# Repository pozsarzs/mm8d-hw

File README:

*** WARNING! It is not yet useable, because it is under development. WARNING ***

Short information
-----------------
MM8D/PC * Growing house controlling and remote monitoring device
Copyright (C) 2020 Pozsár Zsolt <pozsar.zsolt@szerafingomba.hu>
Homepage: <http://www.szerafingomba.hu/equipments/>

Documentation
 - version:             1.0
 - licence:             CC-BY-NC-4.0
 - language:            en

Hardware
 - version:             vyymmdd
 - architecture:        i386
 - operation system:    FreeDOS

Software
 - version:             v0.1
 - licence:             EUPL v1.1
 - language:            en

External libraries in package

*** WARNING! It is not yet useable, because it is under development. WARNING ***

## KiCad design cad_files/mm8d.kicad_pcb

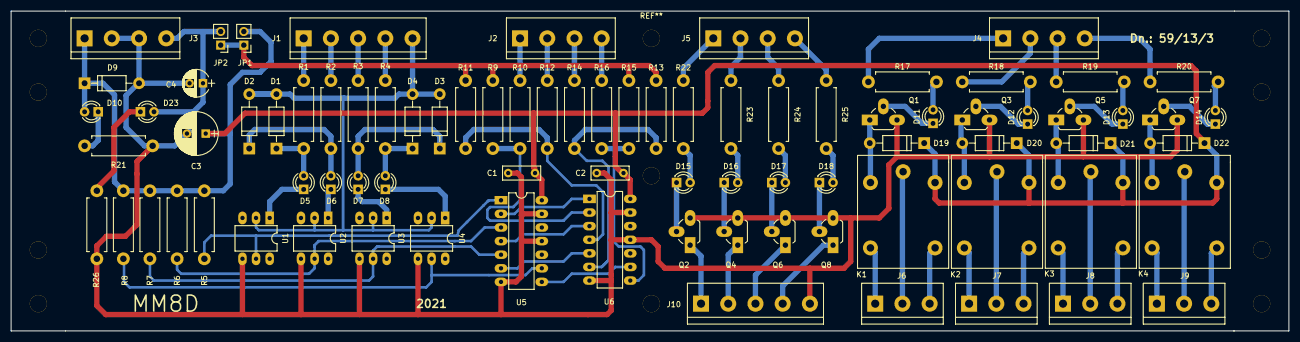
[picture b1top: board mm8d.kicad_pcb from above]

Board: 2 copper layers, 238.5 x 59.7 mm, 83 parts (0 on the bottom side), 79 nets.

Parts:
C1, C2: 100n; C_Rect_L7.0mm_W2.5mm_P5.00mm
C3: 470u; CP_Radial_D8.0mm_P3.50mm
C4: 4.7u; CP_Radial_D5.0mm_P2.50mm
D1, D2, D3, D4, D9, D19, D20, D21, D22: 1N4001; D_DO-41_SOD81_P10.16mm_Horizontal
D5, D6, D7, D8, D10, D11, D12, D13, D14, D15, D16, D17, D18, D23: LED; LED_D3.0mm
J1, J10: Screw_Terminal_1x05; bornier5
J2, J3, J4, J5: Screw_Terminal_1x04; bornier4
J6, J7, J8, J9: Screw_Terminal_1x03; bornier3
JP1: Jumper_NC_Small; Socket_Strip_Straight_1x02_Pitch2.54mm
JP2: Jumper_NO_Small; Socket_Strip_Straight_1x02_Pitch2.54mm
K1, K2, K3, K4: LEG-5; relay_leg
Q1, Q2, Q3, Q4, Q5, Q6, Q7, Q8: BC548C; TO-92_Rugged
R1, R2, R3, R4: 3.9k; R_Axial_DIN0411_L9.9mm_D3.6mm_P12.70mm_Horizontal
R5, R6, R7, R8, R9, R11, R13, R15: 4.7k; R_Axial_DIN0411_L9.9mm_D3.6mm_P12.70mm_Horizontal
R10, R12, R14, R16: 750; R_Axial_DIN0411_L9.9mm_D3.6mm_P12.70mm_Horizontal
R17, R18, R19, R20, R22, R23, R24, R25, R26: 620; R_Axial_DIN0411_L9.9mm_D3.6mm_P12.70mm_Horizontal
R21: 1k; R_Axial_DIN0411_L9.9mm_D3.6mm_P12.70mm_Horizontal
U1, U2, U3, U4: 4N25; DIP-6_W7.62mm_LongPads
U5: 74LS14; DIP-14_W7.62mm_LongPads
U6: 74LS05; DIP-14_W7.62mm_LongPads

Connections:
GND: C1.2, C2.2, C3.2, C4.2, D9.2, J3.2, J3.3, J10.5, Q1.3, Q2.3, Q3.3, Q4.3, Q5.3, Q6.3, Q7.3, Q8.3, R21.2, R26.2, U1.4, U2.4, U3.4, U4.4, U5.7, U5.11, U5.13, U6.7, U6.11, U6.13
unnamed: C4.1, D23.2, J3.4, JP2.2
unnamed: D1.1, D5.2, R1.1
unnamed: D1.2, D2.2, D3.2, D4.2, J1.5, U1.2, U2.2, U3.2, U4.2
unnamed: D2.1, D6.2, R2.1
unnamed: D3.1, D7.2, R3.1
unnamed: D4.1, D8.2, R4.1
unnamed: D5.1, U1.1
unnamed: D6.1, U2.1
unnamed: D7.1, U3.1
unnamed: D8.1, U4.1
unnamed: D10.1, R21.1
unnamed: D11.1, Q1.2
unnamed: D11.2, R17.2
unnamed: D12.1, Q3.2
unnamed: D12.2, R18.2
unnamed: D13.1, Q5.2
unnamed: D13.2, R19.2
unnamed: D14.1, Q7.2
unnamed: D14.2, R20.2
unnamed: D15.1, Q2.2
unnamed: D15.2, R22.2
unnamed: D16.1, Q4.2
unnamed: D16.2, R23.2
unnamed: D17.1, Q6.2
unnamed: D17.2, R24.2
unnamed: D18.1, Q8.2
unnamed: D18.2, R25.2
unnamed: D19.2, K1.2, Q1.1
unnamed: D20.2, K2.2, Q3.1
unnamed: D21.2, K3.2, Q5.1
unnamed: D22.2, K4.2, Q7.1
unnamed: D23.1, R26.1
unnamed: J1.1, R1.2
unnamed: J1.2, R2.2
unnamed: J1.3, R3.2
unnamed: J1.4, R4.2
unnamed: J2.1, R10.1
unnamed: J2.2, R12.1
unnamed: J2.3, R14.1
unnamed: J2.4, R16.1
unnamed: J4.1, R17.1
unnamed: J4.2, R18.1
unnamed: J4.3, R19.1
unnamed: J4.4, R20.1
unnamed: J5.1, R22.1
unnamed: J5.2, R23.1
unnamed: J5.3, R24.1
unnamed: J5.4, R25.1
unnamed: J6.1, K1.5
unnamed: J6.2, K1.3
unnamed: J6.3, K1.4
unnamed: J7.1, K2.5
unnamed: J7.2, K2.3
unnamed: J7.3, K2.4
unnamed: J8.1, K3.5
unnamed: J8.2, K3.3
unnamed: J8.3, K3.4
unnamed: J9.1, K4.5
unnamed: J9.2, K4.3
unnamed: J9.3, K4.4
unnamed: J10.1, Q2.1
unnamed: J10.2, Q4.1
unnamed: J10.3, Q6.1
unnamed: J10.4, Q8.1
unnamed: JP1.1, JP2.1, R9.1, R11.1, R13.1, R15.1
unnamed: R5.2, U1.5, U5.1
unnamed: R6.2, U2.5, U5.3
unnamed: R7.2, U3.5, U5.5
unnamed: R8.2, U4.5, U5.9
unnamed: R9.2, R10.2, U6.2
unnamed: R11.2, R12.2, U6.4
unnamed: R13.2, R14.2, U6.6
unnamed: R15.2, R16.2, U6.8
unnamed: U5.2, U6.1
unnamed: U5.4, U6.3
unnamed: U5.6, U6.5
unnamed: U5.8, U6.9
VCC: C1.1, C2.1, C3.1, D9.1, D10.2, D19.1, D20.1, D21.1, D22.1, J3.1, JP1.2, K1.1, K2.1, K3.1, K4.1, R5.1, R6.1, R7.1, R8.1, U5.14, U6.14

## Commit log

2020-07-21 200721
2020-07-25 200725
2020-08-13 200813
2021-01-08 210109
2021-01-10 210110
2021-03-25 210325
2021-03-26 210326
2021-03-26 210305
2021-03-27 210327
2021-04-07 210407
2021-04-13 210413
2021-05-04 210504
2022-03-30 220330
2022-08-05 220805
2023-03-31 230331
2023-09-07 230907
